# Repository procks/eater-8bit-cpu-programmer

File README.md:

# eater-8bit-cpu-programmer
Programmer for Ben Eater 8-bit computer

The programmer has 4 sample programs that can be selected with a button. It also allows programming via a serial terminal. it's used cheap CH32X033F8P6 microcontroller.

Data, Address and Write directly connected to DIP switches and Write button. For programming, all DIP switches must be set to the **up position** (If it's not the LED will light up) and the CPU must be in programming mode. Then press the left button.

Pre-programmed samples:
- Fibonacci
- Double
- FizzBuzz prints each number 1 to 255, printing 0 if the number is divisible by 3 and printing 255 if the number is divisible by 5 (required [additional instructions](https://github.com/procks/eater-8bit-cpu-programmer/tree/main/software/microcode-eeprom-programmer))
- Counts up to 255 and then counts down to 0

Also, a prime number generation program can be added with a 6-step modification, see [reddit post](https://www.reddit.com/r/beneater/comments/1lnd37j/primes_on_the_8bit_cpu/).

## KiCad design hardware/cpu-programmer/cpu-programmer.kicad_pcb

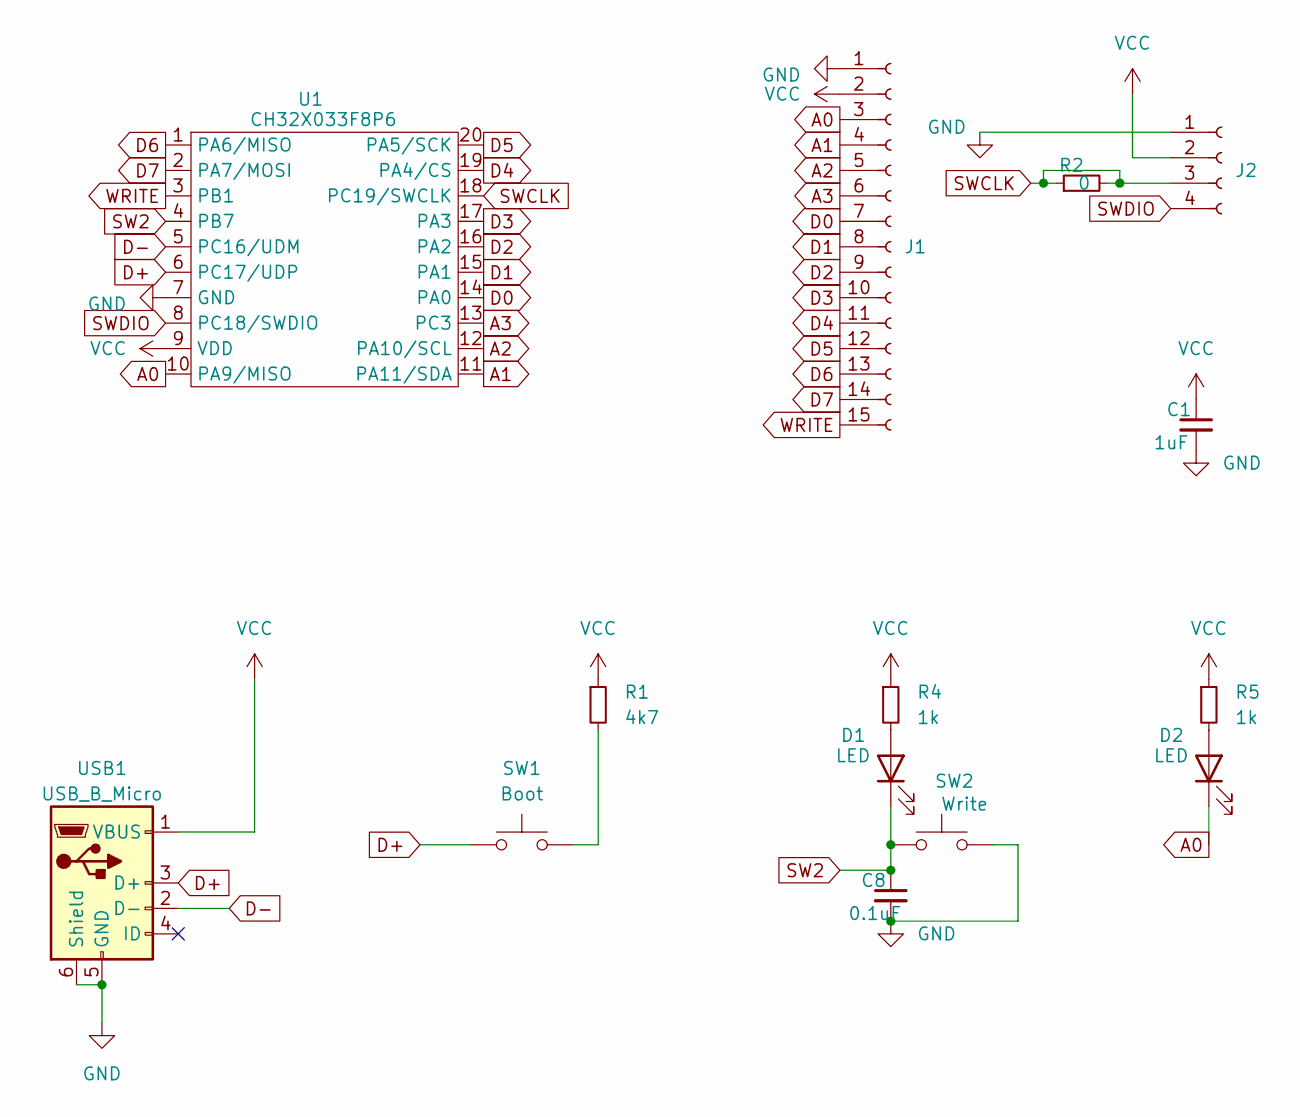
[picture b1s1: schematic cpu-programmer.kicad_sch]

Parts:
C1: 1uF; C_0603_1608Metric
C8: 0.1uF; C_0603_1608Metric
D1, D2: LED; LED_0603_1608Metric
J1: Conn_01x15_Socket; PinHeader_1x15_P2.54mm_Vertical
J2: Conn_01x04_Socket; PinSocket_1x04_P2.54mm_Vertical
R1: 4k7; R_0603_1608Metric
R2: 0; R_1206_3216Metric
R4, R5: 1k; R_0603_1608Metric
SW1: Boot; SW_Push_1P1T_NO_Vertical_4Pins
SW2: Write; SW_Push_1P1T_NO_Vertical_4Pins
U1: CH32X033F8P6; TSSOP-20_4.4x6.5mm_P0.65mm
USB1: USB_B_Micro; USB_Micro-B_Molex-105017-0001

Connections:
A0: D2.1 (K), J1.3, U1.10 (PA9/MISO)
A1: J1.4, U1.11 (PA11/SDA)
A2: J1.5, U1.12 (PA10/SCL)
A3: J1.6, U1.13 (PC3)
D0: J1.7, U1.14 (PA0)
D1: J1.8, U1.15 (PA1)
D2: J1.9, U1.16 (PA2)
D3: J1.10, U1.17 (PA3)
D4: J1.11, U1.19 (PA4/CS)
D5: J1.12, U1.20 (PA5/SCK)
D6: J1.13, U1.1 (PA6/MISO)
D7: J1.14, U1.2 (PA7/MOSI)
D+: SW1.1, U1.6 (PC17/UDP), USB1.3 (D+)
D-: U1.5 (PC16/UDM), USB1.2 (D-)
GND: C1.2, C8.2, J1.1, J2.1, SW2.2, U1.7 (GND), USB1.5 (GND), USB1.6 (Shield)
unnamed: D1.2 (A), R4.2
unnamed: D2.2 (A), R5.2
unnamed: R1.2, SW1.2
SW2: C8.1, D1.1 (K), SW2.1, U1.4 (PB7)
SWCLK: J2.3, R2.1, R2.2, U1.18 (PC19/SWCLK)
SWDIO: J2.4, U1.8 (PC18/SWDIO)
VCC: C1.1, J1.2, J2.2, R1.1, R4.1, R5.1, U1.9 (VDD), USB1.1 (VBUS)
WRITE: J1.15, U1.3 (PB1)

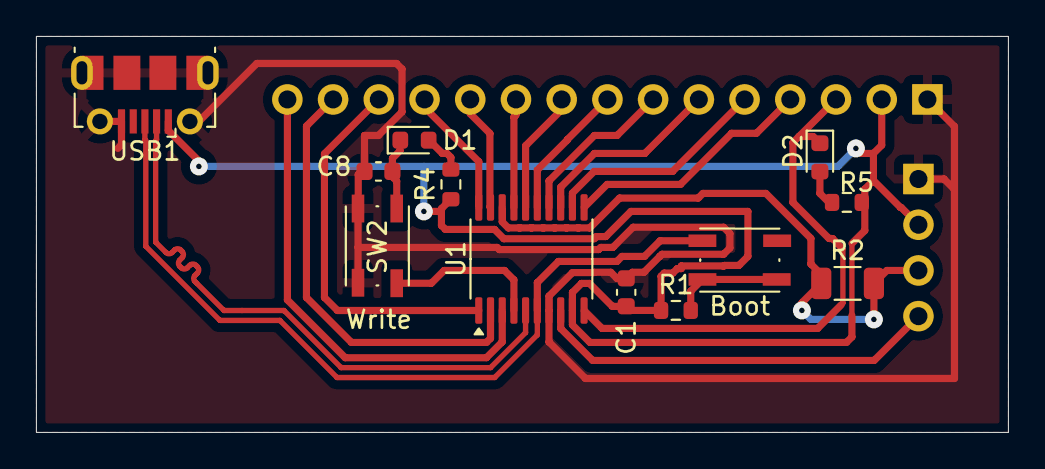
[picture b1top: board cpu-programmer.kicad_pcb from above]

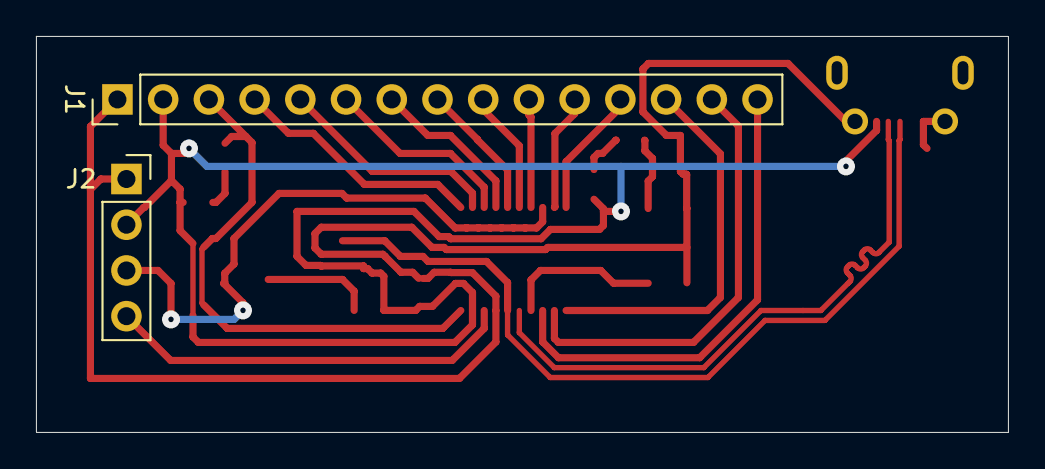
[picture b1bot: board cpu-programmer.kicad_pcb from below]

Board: 2 copper layers, 54.0 x 22.0 mm, 14 parts (2 on the bottom side), 23 nets.

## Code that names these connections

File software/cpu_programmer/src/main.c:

#include <system.h>
#include <gpio.h>
#include <stdbool.h>
#include <console.h>

#define LED PA9
#define LED2 PB7
#define SW1 PC17
#define SW2 PB7
#define DATA0 PA0
#define DATA1 PA1
#define DATA2 PA2
#define DATA3 PA3
#define DATA4 PA4
#define DATA5 PA5
#define DATA6 PA6
#define DATA7 PA7
#define ADDRESS0 PA9
#define ADDRESS1 PA11
#define ADDRESS2 PA10
#define ADDRESS3 PC3
#define WRITE PB1

int dataMap[8] = { DATA0, DATA1, DATA2, DATA3, DATA4, DATA5, DATA6, DATA7 };
int addressMap[8] = { ADDRESS0, ADDRESS1, ADDRESS2, ADDRESS3 };

uint8_t flashProgramm[BLOCK_SIZE];
uint8_t * currentProgram;

// INC (B) intraction (default 5 steps)
uint8_t program0[BLOCK_SIZE] = { 0x51, 0x4e, 0x50, 0x2e, 0x70, 0xe0, 0x4f, 0x1e, 0x4d, 0x1f, 0x4e, 0x1d, 0x63  }; // Fibonacci
uint8_t program1[BLOCK_SIZE] = { 0x51, 0x48, 0xE0, 0x28, 0x70, 0xE0, 0x48, 0x63 }; // Double
uint8_t program2[BLOCK_SIZE] = { 0x1D, 0xB1, 0x4D, 0xC3, 0x8F, 0x73, 0x1D, 0xC5, 0x8E, 0x77, 0x1D, 0xE0, 0x60, 0x00, 0xC1, 0xE0 }; // FizzBuzz
uint8_t program3[BLOCK_SIZE] = { 0xE0, 0x2E, 0x74, 0x60, 0x3F, 0xE0, 0x80, 0x64, 0x00, 0x00, 0x00, 0x00, 0x00, 0x00, 0x01, 0x01 }; // Counts up to 255 and then counts down to 0

// uint8_t program3[BLOCK_SIZE] = { 0x51, 0x47, 0x50, 0xE0, 0x27, 0xE0, 0x64 }; // Count up
// uint8_t program3[BLOCK_SIZE] = { 0x50, 0xB1, 0xE0, 0x61 }; // Test1 inc
// uint8_t program3[BLOCK_SIZE] = { 0xE0, 0x2E, 0x74, 0x60, 0x3F, 0xE0, 0x88, 0x64, 0xF0, 0x00, 0x00, 0x00, 0x00, 0x00, 0x03, 0x06 }; // Counts up to 255 by 3s and then counts down to 0 by 6s
// uint8_t program3[BLOCK_SIZE] = { 0x1F, 0xB1, 0x4F, 0x3E, 0x87, 0x73, 0x60, 0x1F, 0xE0, 0x60, 0x00, 0x00, 0x00, 0x00, 0x03, 0x00 }; // Modulo 3

//ADDS (B) intraction (required 6 steps modification)
// uint8_t program0[BLOCK_SIZE] = { 0x51, 0x4e, 0x50, 0x2e, 0x70, 0xe0, 0x4f, 0x1e, 0x4d, 0x1f, 0x4e, 0x1d, 0x63  }; // Fibonacci
// uint8_t program1[BLOCK_SIZE] = { 0x51, 0xBF, 0x52, 0x4E, 0x1F, 0x3E, 0x80, 0x75, 0x51, 0xBE, 0x3F, 0xA4, 0xDF, 0x60, 0x00, 0x02 }; // Primes
// uint8_t program2[BLOCK_SIZE] = { 0x51, 0xBD, 0xC3, 0x8F, 0x72, 0x1D, 0xC5, 0x8E, 0x76, 0x1D, 0xE0, 0x60, 0x00, 0x00, 0xC1, 0xE0 }; // FizzBuzz
// uint8_t program3[BLOCK_SIZE] = { 0xE0, 0x2E, 0x74, 0x60, 0x3F, 0xE0, 0x80, 0x64, 0x00, 0x00, 0x00, 0x00, 0x00, 0x00, 0x01, 0x01 }; // Counts up to 255 and then counts down to 0

#define PROGRAMS_LEN 4
#define FLASH_PROGRAM_NUM PROGRAMS_LEN - 1
uint8_t* programs[] = { program0, program1, program2, flashProgramm };
int programNum = PROGRAMS_LEN - 1;

void writeLine(int pin, bool value) {
	if (value) {
		PIN_input(pin);
	} else {
		PIN_output(pin);
		PIN_low(pin);
	}
}

void writeData(uint8_t address, uint8_t data) {
	for (int i = 0; i < 4; i++) {
		int bit = (address >> i) & 1;
		writeLine(addressMap[i], bit);
	}
	for (int i = 0; i < 8; i++) {
		int bit = (data >> i) & 1;
		writeLine(dataMap[i], bit);
	}
	
	writeLine(WRITE, false);
	DLY_ms(5);
	writeLine(WRITE, true);
	DLY_ms(5);
}

void setLinesIn() {
	for (int i = 0; i < 4; i++) {
		PIN_input(addressMap[i]);
	}
	for (int i = 0; i < 8; i++) {
		PIN_input(dataMap[i]);
	}
	PIN_input(WRITE);
}

bool checkLines() {
	setLinesIn();
	bool ok = true;
	for (int i = 0; i < 4; i++) {
		if (!PIN_read(addressMap[i])) ok = false;
	}
	for (int i = 0; i < 8; i++) {
		if (!PIN_read(dataMap[i])) ok = false;
	}
	if (!PIN_read(WRITE)) ok = false;
	return ok;
}

void blinkError() {
	PIN_output(LED2);
	for (int i = 0; i < 3; i++) {
		PIN_low(LED2);
		DLY_ms(50);
		//PIN_high(LED2);
		//DLY_ms(50);
	}
	PIN_input_PU(LED2);
  DLY_ms(1);
}

void blinkOk() {
	PIN_output(LED2);
	for (int i = 0; i < 5; i++) {
		PIN_low(LED2);
		DLY_ms(250);
		PIN_high(LED2);
		DLY_ms(250);
	}
	PIN_input_PU(LED2);
}

void printCurrentProgram() {
	if (CDC_ready()) {
		for (int i = 0; i < BLOCK_SIZE; i++) {
			printByte(currentProgram[i]);
			CDC_print(" ");
		}
		CDC_newline();
		CDC_flush();	
	}
}

void writeToCpu() {
	printCurrentProgram();
	// writeLine(LED, false);
	writeLine(addressMap[programNum], false);
	DLY_ms(250);
	// writeLine(LED, true);
	writeLine(addressMap[programNum], true);
	DLY_ms(100);
	for (int a = 0; a < BLOCK_SIZE; a++) {
		writeData(a, currentProgram[a]);
	}
}

void writeFlashProgramToCpu() {
	programNum = FLASH_PROGRAM_NUM;
	currentProgram = programs[programNum];
	writeToCpu();
}

void nextProgram() {
	programNum++;
	if (programNum >= PROGRAMS_LEN) {
		programNum = 0;
	}
	currentProgram = programs[programNum];
	writeToCpu();
}

void initFlashProgram() {
	loadFromFlash();
	// if not found use preset program4
	if (flashProgramm[0] == 0xff) {
		for (int i = 0; i < BLOCK_SIZE; i++) {
			flashProgramm[i] = program3[i];
		}
	}
}

bool lastButtonState = true;
int main() {
	CDC_init();
	// PIN_input_PD(SW1); // USB will not work
	PIN_input_PU(SW2);
	initFlashProgram();
	while(1) {
		if (!checkLines()) {
			blinkError();
		}
		else {
			bool currentState = PIN_read(SW2);
			if (!lastButtonState && currentState) {
				DLY_ms(30); // debounce
				currentState = PIN_read(SW2);
			
				if (currentState) {
					nextProgram();
				}
			}	
			lastButtonState = currentState;
		}
	    consoleRoutine();
	}
}

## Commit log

2025-06-26 Added Microcode Cheat Sheet
2025-06-26 Renamed cpu-programmer-schematic
2025-06-26 Added microcode-eeprom-programmer.ino with extended instruction microcode set
2025-06-26 Clean up schematic
2025-06-27 Updated PCB, parts use at least package 0603
2025-06-27 Added gerber
2025-06-27 Renamed gerber
2025-06-27 Updated PCB
    Fixed silkscreen lables
2025-06-27 Added some resources
2025-06-28 Fixed differential pair
2025-06-28 Fixed serial programming
2025-06-29 Added datasheets
2025-06-29 Added primes program for 6 step modification
2025-06-29 Fixed Microcode Cheat Sheet_experimental.xlsx
